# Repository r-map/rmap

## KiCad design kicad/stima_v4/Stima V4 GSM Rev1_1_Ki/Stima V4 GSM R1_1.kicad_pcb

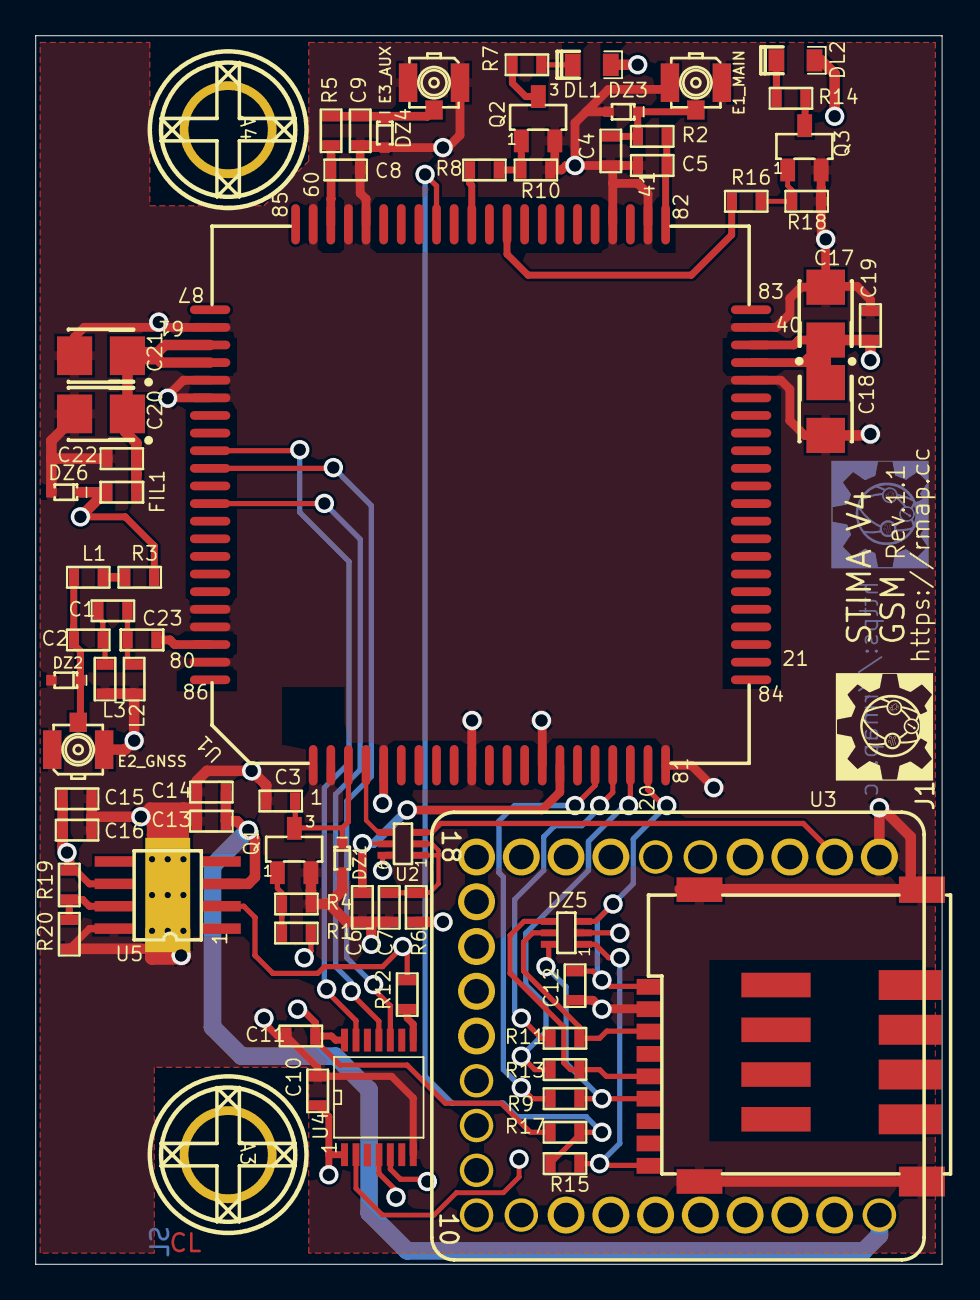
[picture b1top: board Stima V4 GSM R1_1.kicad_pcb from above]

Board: 4 copper layers, 51.4 x 69.7 mm, 69 parts (0 on the bottom side), 47 nets.

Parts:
A3, A4: ViteDado; ViteDado4
C1, C23: 0R; 0603
C2: 33pF; 0603
C3, C6, C7, C10, C11, C12, C13, C15, C19, C22: 100n; 0603
C4, C5, C8, C9: NM; 0603
C14, C16: 10uF; 0603
C17, C18, C20, C21: 100uF 10V; Case B-TC3528-1411
DL1: BLU; 0805-led
DL2: GREEN; 0805-led
DZ1: PESD5Z3.3; SOD 523(SC-79)
DZ2, DZ3, DZ4, DZ6: PESD5Z5.0; SOD 523(SC-79)
DZ5: ESDA6V1-5W6; SOT363(SC70)
E1_MAIN, E2_GNSS, E3_AUX: RECE.20279.001E.01; CONN_ANTENNA_SMD
FIL1: BLM18PG; 0603
J1: SIM7100-6-1-15-00-A; SIM CARD MICRO
L1: 7447860147G; 0603
L2, L3: NM; 0603
Q1: BSS138P; SOT23
Q2, Q3: BC817; SOT23
R1, R8, R16: 4K7; 0603
R2, R5, R13: 0R; 0603
R3: 10R; 0603
R4, R10, R17, R18: 47K; 0603
R6: 200K; 0603
R7, R14: 2K2; 0603
R9, R11, R15: 22R; 0603
R12: 47R; 0603
R19: 100K; 0603
R20: 15K; 0603
U1: SIM7600E S2-107EP-Z304M; SIM7600
U2: LSF0101GWH; SOT363(SC70)
U3: UPIN27; UPIN27_OK
U4: TXU0204; TSSOP14
U5: SC4216; SO8-EDP-2 MIO

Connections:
+1V8: C6.1, C11.1, R17.2, U1.15, U2.5, U4.14
+3V3: C10.1, R6.2, U3.2, U4.1
+3V8: C15.1, C16.1, C17.1, C18.1, C19.1, DL1.2, DL2.2, DZ6.1, FIL1.1, R3.1, R19.2, U1.38, U1.39, U5.6
+5V: C13.1, C14.1, U3.1, U5.3
EN_PW_GSM: R12.2, U3.23, U5.2
GND: C3.2, C4.2, C5.2, C6.2, C7.2, C8.2, C9.2, C10.2, C11.2, C12.2, C13.2, C14.2, C15.2, C16.2, C17.2, C18.2, C19.2, C20.2, C21.2, C22.2, DZ1.2, DZ2.2, DZ3.2, DZ4.2, DZ5.2, DZ6.2, E1_MAIN.2, E2_GNSS.2, E3_AUX.2, J1.C5, J1.GND, L2.1, L3.1, Q1.2, Q2.2, Q3.2, R4.1, R10.1, R18.1, R20.1, U1.1, U1.2, U1.5, U1.10, U1.14, U1.37, U1.40, U1.41, U1.43, U1.57, U1.58, U1.60, U1.61, U1.64, U1.65, U1.77, U1.78, U1.80, U1.81, U2.6, U3.27, U4.7, U5.0, U5.8, U5.9
NetC1_1: C1.1, C23.2, L2.2
NetC1_2: C1.2, C2.1, L3.2
NetC2_2: C2.2, DZ2.1, E2_GNSS.1, L1.1
NetC3_1: C3.1, DZ1.1, Q1.3, U1.3
NetC4_1: C4.1, DZ3.1, E1_MAIN.1, R2.2
NetC5_1: C5.1, R2.1, U1.82
NetC7_1: C7.1, R6.1, U2.1, U2.2
NetC8_1: C8.1, R5.2, U1.59
NetC9_1: C9.1, DZ4.1, E3_AUX.1, R5.1
NetC12_1: C12.1, DZ5.3, J1.C1, U1.20
NetC20_1: C20.1, C21.1, C22.1, FIL1.2, U1.62, U1.63
NetC23_1: C23.1, U1.79
NetDL1_1: DL1.1, R7.1
NetDL2_1: DL2.1, R14.1
NetDZ5_1: DZ5.1, J1.CD, R15.2
NetDZ5_4: DZ5.4, J1.C3, R13.2
NetDZ5_5: DZ5.5, J1.C2, R11.2
NetDZ5_6: DZ5.6, J1.C7, R9.2
NetL1_2: L1.2, R3.2
NetQ1_1: Q1.1, R1.1, R4.2
NetQ2_1: Q2.1, R8.1, R10.2
NetQ2_3: Q2.3, R7.2
NetQ3_1: Q3.1, R16.1, R18.2
NetQ3_3: Q3.3, R14.2
NetR8_2: R8.2, U1.51
NetR9_1: R9.1, U1.17
NetR11_1: R11.1, U1.18
NetR12_1: R12.1, U4.8
NetR13_1: R13.1, U1.19
NetR15_1: R15.1, R17.1, U1.53
NetR19_1: R19.1, R20.2, U5.7
NetU1_4: U1.4, U2.4
NetU1_68: U1.68, U4.13
NetU1_69: U1.69, U4.10
NetU1_71: U1.71, U4.11
PWRKEY: R1.2, U3.24
RI: U3.21, U4.5
RST: U2.3, U3.26
STATUS: R16.2, U1.49
USART2_RX: U3.19, U4.4
USART2_TX: U3.20, U4.2

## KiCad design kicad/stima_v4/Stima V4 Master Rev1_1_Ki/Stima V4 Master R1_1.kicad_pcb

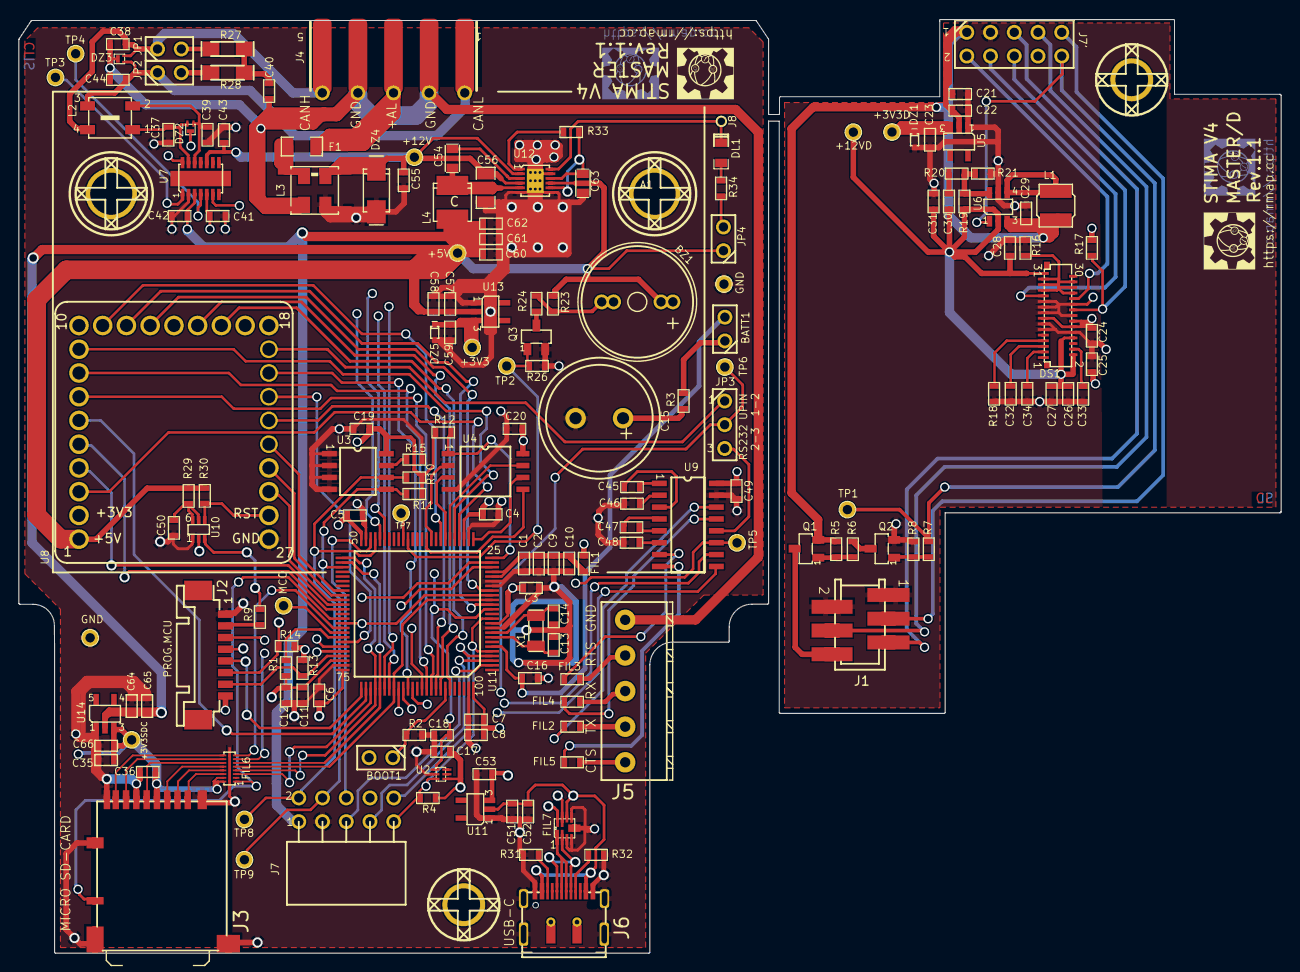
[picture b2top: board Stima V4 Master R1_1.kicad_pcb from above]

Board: 6 copper layers, 135.0 x 99.9 mm, 173 parts (0 on the bottom side), 134 nets.

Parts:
+3V3, +3V3D, +3V3SDC, +5V, +12V, +12VD: TestPoint; TP
A: Comment; _Altium_ARGO_ARGO PcbLib-Trad1.PcbLib_ViteDado4
A1: ViteDado; ViteDado4
A2, A3: ViteDado; _Altium_Library_ARGO_ARGO PcbLib-Trad1.PcbLib_ViteDado3
BATT1: Strip 2p p.2.54; STRIP2P
BOOT1: Strip 2p p.2.54; STRIP2P
BZ1: F/UCW03 (2-5V); BUZZER TDK PS1240P02CT3
C1, C3, C4, C5, C6, C7, C9, C11, C16, C17, C18, C19, C20, C22, C24, C25, C27, C28, C36, C40, C41, C42, C43, C45, C46, C47, C48, C49, C50, C52, C58, C65: 100n; 0603
C2, C10, C21, C23, C26, C29, C31, C51, C53, C57, C59, C64, C66: 1uF; 0603
C8, C12, C32, C33, C34, C35: 4.7u; 0603
C13, C14: 15pF; 0603
C15: 0.1F 5V5 FT0H104ZF; CapELSUPERCAP-3D FT0H104ZF
C30: 22p; 0603
C37, C38, C39, C44: 220p; 0603
C54: 100n; 0805
C55: 1nF; 0603
C56: 4.7u35V; 1206
C60, C61, C62: 10uF; 0603
C63: 1uF; 0805
DL1: GREEN; 0805-led
DS1: REX160128AYPP3N00000; CONN FPC_FFC 31P P0.3 REVERSE-MIO
DZ1, DZ5: PESD5Z3.3; SOD 523(SC-79)
DZ2, DZ3: ESDCAN03; QFN-3L-DFN1110-MIO
DZ4: SMAJ28A; SMA
F1: NSMF150; 1206
FIL1: BLM18BD; 0603
FIL2, FIL3, FIL4, FIL5: BLM18BD102SN1D; 0603
FIL6: EMIF06-; EMIF06MSD02N16-MIO
FIL7: EMI2121MTTAG; WDFN8 - MIO
GND: TestPoint; TP
GND#2: TestPoint; TP
J1: ENCODER+PB 62AG22-L5-040C; CONN MICROMATCH6PF MIO
J2: Pico Blade 8p 53398-0871; MOLEX8P1_25SMD
J3: 101019966912A AMPHENOL; SD CARD MICRO HIROSE MIO
J4: 5P BUS; CONTATTI5
J5: 5P; CONN_5P-P381
J6: USB TYPE C; USB TYPE C 16PIN MIO
J7: Strip 5x2-DF 90 p.2.54; _Altium_Library_ARGO_ARGO PcbLib-Trad1.PcbLib_STRIP2F5X2P2_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
J7': Strip 5x2-DF p.2.54; _Altium_Library_ARGO_ARGO PcbLib-Trad1.PcbLib_STRIP2F5X2P2_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
J8: VIAS1; VIAS0_8
JP1, JP2, JP4: Strip 2p PTH; STRIP2P
JP3: Strip 3p PTH; STRIP3PP254
L1: TYS4018; COIL LAIRD TYS4018
L2: ACT45B-110; ACT45B TDK-MIO
L3: DLW5BTM; FILTRO DLW5B MIO
L4: XAL4020; COIL COILCRAFT XAL4020-MIO
MCO: TestPoint; TP
Q1: BC807; SOT23
Q2, Q3: BSS138P; SOT23
R1: NM; 0603
R2, R4, R13: 100K; 0603
R3, R6, R23, R34: 1K; 0603
R5, R8, R12, R14, R15, R16, R17, R21, R26, R30, R33: 10K; 0603
R7: 100R; 0603
R9, R24: 0R; 0603
R10, R11, R20: 2K2; 0603
R18: 810K; 0603
R19: 110K; 0603
R27, R28: MMA0204 60R4; MELFRESMMA0204
R29: 200K; 0603
R31, R32: 5K11; 0603
TP1, TP2, TP3, TP4, TP5, TP6, TP7, TP8, TP9: TestPoint; TP
U1: STM32L496VGT6; LQFP100P05
U2: STM6519; UDFN6 - MIO
U3: CAT24C64WI; SO8
U4: AT25SF641B; SO8W
U5, U11, U13, U14: ST732M33R; SOT23_5
U6: R1202N513B; SOT23_6
U7: TJA1443ATK; HVSON14 MIO
U8: UPIN27; UPIN27_OK
U9: TRSF3232EIDR; SO16
U10: LSF0101GWH; SOT363(SC70)
U12: MAX20077; TDFN 12L MIO
X1: 32.768KHz; CRYST_ECS

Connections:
3V3USB: C11.1, C12.2, C53.1, R1.1, U1.73, U11.3
+3V3: +3V3.1, BOOT1.2, C3.2, C4.2, C5.2, C6.2, C7.2, C8.2, C17.1, C19.1, C20.1, C41.1, C49.1, C59.1, DZ5.1, FIL1.1, J2.8, R4.2, R10.2, R11.2, R12.1, R13.2, R14.2, U1.11, U1.28, U1.50, U1.75, U1.100, U2.4, U3.8, U4.8, U7.5, U8.2, U9.16, U10.2, U13.3
+3V3D: +3V3D.1, C23.1, C24.1, C25.1, DS1.12, DS1.14, DS1.15, DZ1.1, R17.1, U5.3
+3V3SDC: +3V3SDC.1, C35.1, C36.1, C66.1, FIL6.15, FIL6.16, J3.4, U14.3
+5V: +5V.1, BZ1.1, C21.1, C22.1, C29.1, C42.1, C57.1, C58.1, C60.2, C61.2, C62.2, C64.1, C65.1, J7.1, J7'.1, JP4.1, L1.1, L4.2, Q1.2, R5.2, R23.2, R29.2, R30.2, U5.2, U6.3, U7.3, U8.1, U12.9, U13.2, U14.2
+5VE: J1.6, Q1.3
+12V: +12V.1, C43.2, C55.1, C56.1, DZ4.1, L3.2, U7.10, U12.2, U12.4
+12VD: +12VD.1, C26.2, C27.2, C28.2, C30.1, C31.1, DS1.2, DS1.8, DS1.31, R19.1, U6.2
+AL: F1.1, J4.3
-RESET: C18.1, R9.1, U1.14, U2.1, U10.3
CANH: C38.2, DZ3.2, J4.5, JP1.1, L2.4
CANL: C44.2, DZ3.1, J4.1, JP2.1, L2.3
EGND: C38.1, C40.1, C44.1, DZ3.3, J4.2, J4.4, J5.5, L3.4
EN+5VE: J7.10, J7'.10, R7.2, TP1.1, U1.4, U6.1
ENC_A: J1.5, J7.5, J7'.5, U1.2
ENC_B: J1.4, J7.7, J7'.7, U1.3
GND: C1.1, C2.2, C3.1, C4.1, C5.1, C6.1, C7.1, C8.1, C9.1, C10.2, C11.2, C12.1, C13.2, C14.2, C15.2, C16.1, C17.2, C18.2, C19.2, C20.2, C21.2, C22.2, C23.2, C24.2, C25.2, C26.1, C27.1, C28.1, C29.2, C31.2, C32.2, C33.2, C34.2, C35.2, C36.2, C37.1, C39.1, C41.2, C42.2, C43.1, C46.1, C48.1, C49.2, C50.1, C51.2, C52.2, C53.2, C55.2, C56.2, C57.2, C58.2, C59.2, C60.1, C61.1, C62.1, C63.2, C64.2, C65.2, C66.2, DS1.10, DS1.11, DS1.13, DS1.16, DS1.17, DS1.19, DS1.20, DS1.21, DZ1.2, DZ2.3, DZ4.2, DZ5.2, FIL6.17, FIL7.3, FIL7.4, FIL7.5, FIL7.GND, GND.1, GND#2.1, J1.1, J1.2, J2.1, J3.6, J3.CD2, J3.SCH, J6.0, J6.A1, J6.A12, J6.B1, J6.B12, J7.3, J7'.3, L3.3, Q2.2, Q3.2, R2.1, R8.2, R15.1, R16.2, R18.1, R21.2, R26.1, R31.1, R32.2, U1.10, U1.19, U1.20, U1.27, U1.49, U1.74, U1.99, U2.2, U3.1, U3.2, U3.3, U3.4, U4.4, U5.1, U6.5, U7.2, U8.27, U9.15, U10.1, U11.1, U12.6, U12.7, U12.11, U12.13, U13.1, U14.1
KEY1: J1.3, J7.9, J7'.9, R4.1, U1.5, U1.12, U2.3
NetBATT1_1: BATT1.1, R3.1
NetBATT1_2: BATT1.2, C16.2, U1.6
NetBOOT1_1: BOOT1.1, R2.2, U1.94
NetBZ1_2: BZ1.2, R23.1, R24.1
NetC1_2: C1.2, C2.1, C9.2, C10.1, FIL1.2, U1.21, U1.22
NetC13_1: C13.1, U1.8, X1.2
NetC14_1: C14.1, U1.9, X1.1
NetC15_1: C15.1, R3.2
NetC30_2: C30.2, R20.1
NetC32_1: C32.1, DS1.5
NetC33_1: C33.1, DS1.4
NetC34_1: C34.1, DS1.3
NetC37_2: C37.2, DZ2.2, L2.1, U7.13
NetC39_2: C39.2, DZ2.1, L2.2, U7.12
NetC40_2: C40.2, R27.1, R28.2
NetC45_1: C45.1, U9.3
NetC45_2: C45.2, U9.1
NetC46_2: C46.2, U9.2
NetC47_1: C47.1, U9.5
NetC47_2: C47.2, U9.4
NetC48_2: C48.2, U9.6
NetC50_2: C50.2, R29.1, U10.5, U10.6
NetC51_1: C51.1, C52.1, FIL7.6, J6.A4, J6.A9, J6.B4, J6.B9, U11.2
NetC54_1: C54.1, U12.3
NetC54_2: C54.2, L4.1, U12.5
NetC63_1: C63.1, R33.1, U12.8, U12.10
NetDL1_1: DL1.1, J8.1, U12.12
NetDL1_2: DL1.2, R34.1
NetDS1_7: DS1.7, R18.2
NetDS1_18: DS1.18, J7.6, J7'.6, R17.2, U1.48
NetDS1_24: DS1.24, DS1.25, DS1.26, DS1.27, DS1.28, DS1.29, R16.1
NetF1_2: F1.2, L3.1
NetFIL2_1: FIL2.1, U9.14
NetFIL2_2: FIL2.2, J5.2
NetFIL3_1: FIL3.1, U9.7
NetFIL3_2: FIL3.2, J5.4
NetFIL4_1: FIL4.1, U9.13
NetFIL4_2: FIL4.2, J5.3
NetFIL5_1: FIL5.1, U9.8
NetFIL5_2: FIL5.2, J5.1
NetFIL6_1: FIL6.1, J3.CD1, U1.64
NetFIL6_3: FIL6.3, U1.78
NetFIL6_8: FIL6.8, U1.66
NetFIL6_9: FIL6.9, J3.8
NetFIL6_10: FIL6.10, J3.7
NetFIL6_11: FIL6.11, J3.5
NetFIL6_12: FIL6.12, J3.3
NetFIL6_13: FIL6.13, J3.2
NetFIL6_14: FIL6.14, J3.1
NetFIL7_1: FIL7.1, J6.A6, J6.B6
NetFIL7_2: FIL7.2, J6.A7, J6.B7
NetFIL7_7: FIL7.7, U1.70
NetFIL7_8: FIL7.8, U1.71
NetJ2_2: J2.2, R9.2
NetJ6_A5: J6.A5, R31.2
NetJ6_B5: J6.B5, R32.1
NetJP1_2: JP1.2, R27.2
NetJP2_1: JP2.2, R28.1
NetJP3_2: JP3.2, TP6.1, U1.87
NetJP3_3: JP3.3, U9.12
NetJP4_2: JP4.2, R34.2
NetL1_2: L1.2, U6.4
NetMCO_1: MCO.1, U1.67
NetQ1_1: Q1.1, R5.1, R6.1
NetQ2_1: Q2.1, R7.1, R8.1
NetQ2_3: Q2.3, R6.2
NetQ3_1: Q3.1, R26.2, TP2.1, U1.40
NetQ3_3: Q3.3, R24.2
NetR1_2: R1.2, U1.68
NetR15_2: R15.2, U3.7
NetR19_2: R19.2, R20.2, R21.1, U6.6
NetR33_2: R33.2, U12.1
NetTP3_1: TP3.1, U1.82, U7.1
NetTP4_1: TP4.1, U1.81, U7.4
NetTP7_1: TP7.1, U1.41
NetU1_15: U1.15, U8.12
NetU1_18: U1.18, U8.13
NetU1_29: U1.29, U8.3
NetU1_30: U1.30, U8.9
NetU1_33: U1.33, U8.11
NetU1_45: U1.45, U7.6
NetU1_46: U1.46, U7.14
NetU1_58: U1.58, U8.23
NetU1_59: U1.59, U8.24
NetU1_60: U1.60, U8.25
NetU1_61: U1.61, U8.4
NetU1_62: U1.62, U8.5
NetU1_69: U1.69, U8.21
NetU1_77: U1.77, U8.6
NetU1_84: U1.84, U9.9
NetU1_85: U1.85, U9.10
NetU1_90: U1.90, U8.8
NetU1_91: U1.91, U8.7
NetU1_92: U1.92, U8.22
NetU1_93: U1.93, U8.15
NetU1_95: U1.95, U8.16
PA2/F_-CS: R12.2, U1.25, U4.1
PA3/F_SCK: U1.26, U4.6
PA6/F_I/O3: U1.31, U4.7
PA7/F_I/O2: U1.32, U4.3
PA13/SWDIO: J2.7, R13.1, U1.72
PA14/SWCLK: J2.5, U1.76
PB0/F_I/O1: U1.35, U4.2
PB1/F_I/O0: U1.36, U4.5
PB3/SWO: J2.3, U1.89
PB10/I2C2_SCL: DS1.22, J7.2, J7'.2, R10.1, TP8.1, U1.47, U3.6
PB14/I2C2_SDA: DS1.23, J7.4, J7'.4, R11.1, TP9.1, U1.53, U3.5
RST: R30.1, U8.26, U10.4
SDMMC1_CK: FIL6.6, U1.52, U1.80
SDMMC1_CMD: FIL6.5, U1.16, U1.83
SDMMC1_D0: FIL6.7, U1.17, U1.65
SDMMC1_D3: FIL6.4, U1.51, U1.79
USART2_RX: JP3.1, U8.19
USART2_TX: TP5.1, U1.86, U8.20, U9.11
USART4_RX: J2.6, R14.1, U1.24
USART4_TX: J2.4, U1.23

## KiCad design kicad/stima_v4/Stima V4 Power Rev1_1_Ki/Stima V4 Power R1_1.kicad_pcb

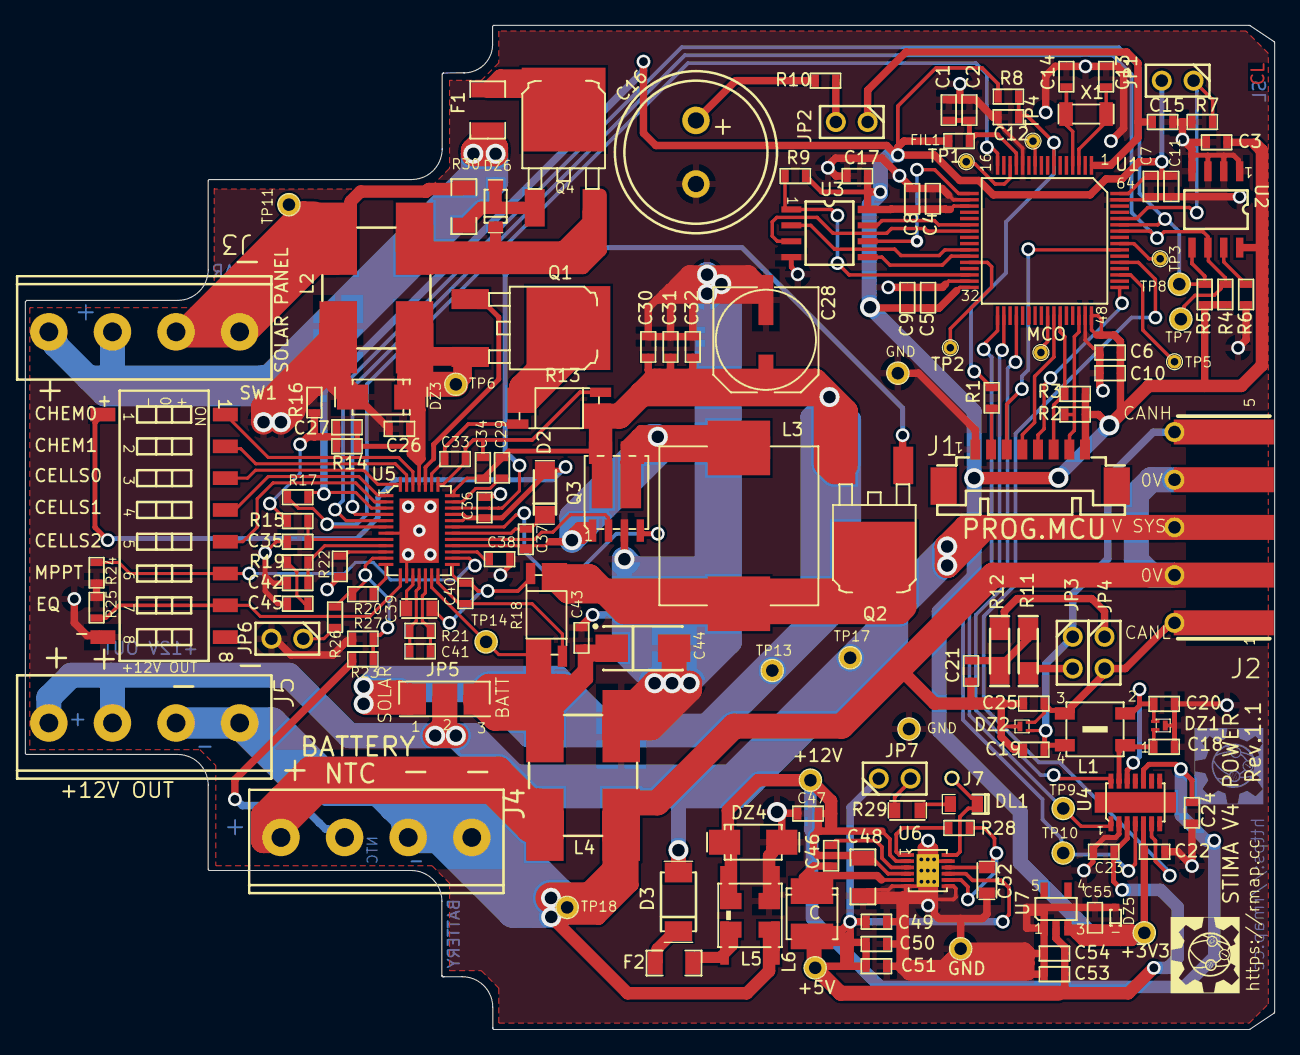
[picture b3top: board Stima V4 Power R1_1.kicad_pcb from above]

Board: 2 copper layers, 99.8 x 80.2 mm, 151 parts (0 on the bottom side), 99 nets.

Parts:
+3V3, +5V, +12V: TestPoint; TP
C1, C8, C9, C10, C11: 4.7uF; 0603
C2, C3, C4, C5, C6, C7, C12, C15, C17, C21, C22, C23, C24, C30, C41, C46, C54: 100nF; 0603
C13, C14: 15pF; 0603
C16: 0.1F 5V5; CapELSUPERCAP-3D FT0H104ZF
C18, C19, C20, C25: 220pF; 0603
C26, C31, C32, C36, C43: 10uF 35V; 0603
C27: 2.2nF; 0603
C28: 100uF 50V; 8X10_5
C29: 330nF; 0603
C33, C40, C47: 1nF; 0603
C34, C53, C55: 1uF; 0603
C35: 100pF; 0603
C37: 470nF; 0603
C38: 2.2uF; 0603
C39: 330nF; 0805
C42: 10nF; 0603
C44: 10uF 25V; Case C-TC6032-2412
C45: 220nF; 0603
C48: 4.7uF 35V; 1206
C49, C50, C51: 10uF; 0603
C52: 1uF; 0805
D2: LL4148; DSOD80
D3: SM4007; QMELFD
DL1: VERDE; 0805-led
DZ1, DZ2: ESDCAN03-2BM3Y; QFN-3L-DFN1110-MIO
DZ3, DZ4: SMAJ28A; SMA
DZ5: PESD5Z3.3; SOD 523(SC-79)
DZ6: BZT52C10; SOD-123
F1: MMF-USML600/6-2; 1210
F2: MF-NSMF150; 1206
FIL1: BLM18BD102SN1D; 0603
GND: TestPoint; TP
GND#2, GND#3: TestPoint; TP
J1: Pico Blade 8p 53398-0871; MOLEX8P1_25SMD
J2: 5P BUS; CONTATTI5
J3, J4, J5: 4P; CONN_4P-P508
J7: VIAS1; VIAS0_8
JP1, JP2, JP3, JP4, JP6: Strip 2p PTH; STRIP2P
JP5: JUMP3S
JP7: Strip 2p trad.; STRIP2P
L1: ACT45B-110-2P-TL003; ACT45B TDK-MIO
L2, L4: SBS9080-509T; FILTRO KEMET SBS9080-MIO
L3: SRP1265A-100M; COIL BOURNS SRP1265A-MIO
L5: DLW5BTM142TQ2L; FILTRO DLW5B MIO
L6: XAL4020-222MEC; COIL COILCRAFT XAL4020-MIO
MCO: TestPoint; TP_P
Q1: DMTH43M8LK3Q-13; TO252 (DPAK)
Q2: SQD40131EL_GE3; TO252 (DPAK)
Q3: DMTH4011SPD-13; POWERDI5060-8-MIO
Q4: DMPH6050SK3-13; TO252 (DPAK)
R1: 0R; 0603
R2, R7, R8: 100K; 0603
R3, R6, R9, R15, R16, R17, R20, R24, R25, R26, R28: 10K; 0603
R4, R5: 2K2; 0603
R10: 1K; 0603
R11, R12: MMA0204 60R4; MELFRESMMA0204
R13, R18: WSK2512 10mOHM; RES CURRSENS 4P WSK2512
R14: 294K; 0603
R19: 200R; 0603
R21: 301K 0.1%; 0603
R22: 95K3; 0603
R23, R27: *; 0603
R29: 1K; 0805
R30: 1K5 1/2W; 1206
SW1: TDS08SGNNTR04; DIPSWITCH8P-TRISTATE
TP1, TP2, TP3, TP4, TP5: TestPoint; TP_P
TP6, TP7, TP8, TP9, TP10, TP11, TP13, TP14, TP17, TP18: TestPoint; TP
U1: STM32L452RCT6; LQFP64
U2: CAT24C64WI; SO8
U3: AT25SF161SSHD; SO8
U4: TJA1443ATK; HVSON14 MIO
U5: LTC4015EUHF#PBF; UHF QFN38 MIO
U6: MAX20077ATCA/VY+; TDFN 12L MIO
U7: ST732M33R; SOT23_5
X1: 32.768KHz; CRYST_ECS

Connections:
+: J4.1, L4.1
+3V3: +3V3.1, C3.1, C4.1, C5.1, C6.1, C7.1, C8.2, C9.2, C10.2, C11.2, C17.1, C22.1, C55.1, DZ5.1, FIL1.1, J1.8, JP1.2, R2.1, R3.1, R4.2, R5.2, R8.2, R9.2, R17.1, U1.19, U1.32, U1.48, U1.64, U2.8, U3.8, U4.5, U5.3, U7.3
+5V: +5V.1, C23.1, C49.2, C50.2, C51.2, C53.1, C54.1, JP7.1, L6.2, U4.3, U6.9, U7.2
+12V: +12V.1, C24.2, C47.1, C48.1, DZ4.1, L5.2, U4.10, U6.2, U6.4
-: C19.1, C21.1, C25.1, DZ2.3, J2.2, J2.4, J4.3, J4.4, J5.3, J5.4, L4.3, L5.4, TP18.1
-RESET: C12.1, R1.1, R8.1, U1.7
CANH: C19.2, DZ2.1, J2.5, JP3.1, L1.4
CANL: C25.2, DZ2.2, J2.1, JP4.2, L1.3
F_-CS: R9.1, U1.30, U3.1
F_I/O0: U1.27, U3.5
F_I/O1: U1.26, U3.2
F_I/O2: U1.23, U3.3
F_I/O3: U1.22, U3.7
F_SCK: U1.17, U3.6
GND: C1.2, C2.2, C3.2, C4.2, C5.2, C6.2, C7.2, C8.1, C9.1, C10.1, C11.1, C12.2, C13.2, C14.2, C15.2, C16.2, C17.2, C18.1, C20.1, C22.2, C23.2, C24.1, C26.2, C28.2, C30.2, C31.2, C32.2, C35.2, C36.2, C38.2, C42.2, C43.2, C44.2, C45.2, C47.2, C48.2, C49.1, C50.1, C51.1, C52.1, C53.2, C54.2, C55.2, DZ1.3, DZ3.2, DZ4.2, DZ5.2, GND.1, GND#2.1, GND#3.1, J1.1, JP6.2, L2.4, L4.4, L5.3, Q3.S2, R6.1, R7.2, R16.1, R22.1, R24.1, R25.1, R27.2, SW1.-, U1.12, U1.18, U1.31, U1.47, U1.63, U2.1, U2.2, U2.3, U2.4, U3.4, U4.2, U5.7, U5.14, U5.39, U6.6, U6.7, U6.11, U6.13, U7.1
I2C1_SCL: R4.1, TP7.1, U1.58, U2.6, U5.4
I2C1_SDA: R5.1, TP8.1, U1.59, U2.5, U5.5
INTVCC: C36.1, D2.2, SW1.+, U5.27, U5.28
NTC: J4.2, R23.1
NetC1_1: C1.1, C2.1, FIL1.2, U1.13
NetC13_1: C13.1, U1.3, X1.2
NetC14_1: C14.1, U1.4, X1.1
NetC15_1: C15.1, JP2.1, U1.1
NetC16_1: C16.1, R10.2
NetC18_2: C18.2, DZ1.2, L1.1, U4.13
NetC20_2: C20.2, DZ1.1, L1.2, U4.12
NetC21_2: C21.2, R11.1, R12.2
NetC26_1: C26.1, C27.1, DZ3.1, L2.2, Q1.3, R14.2, TP6.1, U5.35
NetC27_2: C27.2, R14.1, R15.1, R16.2
NetC28_1: C28.1, C29.1, C30.1, C31.1, C32.1, C34.2, JP5.1, Q2.3, Q3.D1, R13.I2, TP13.1, U5.31
NetC29_2: C29.2, U5.30
NetC33_1: C33.1, R13.E1, U5.33
NetC33_2: C33.2, C34.1, R13.E2, U5.32
NetC35_1: C35.1, R15.2, U5.8
NetC37_1: C37.1, D2.1, U5.25
NetC37_2: C37.2, L3.1, Q3.D2, Q3.S1, U5.23
NetC38_1: C38.1, U5.22
NetC39_1: C39.1, U5.15
NetC39_2: C39.2, C40.1, R18.E1, U5.20
NetC40_2: C40.2, R18.E2, U5.19
NetC41_1: C41.1, R21.2, U5.17
NetC41_2: C41.2, R21.1, U5.16
NetC42_1: C42.1, R19.2, U5.9
NetC43_1: C43.1, C44.1, JP5.3, L4.2, R18.I2, TP14.1, U5.18
NetC45_1: C45.1, R19.1
NetC46_1: C46.1, U6.3
NetC46_2: C46.2, L6.1, U6.5
NetC52_2: C52.2, R28.2, U6.8, U6.10
NetD3_1: D3.1, F2.1
NetDL1_1: DL1.1, J7.1, U6.12
NetDL1_2: DL1.2, R29.1
NetDZ6_1: DZ6.1, L2.1, Q4.3
NetDZ6_2: DZ6.2, Q4.1, R30.2
NetF1_1: F1.1, J3.3, J3.4
NetF1_2: F1.2, Q4.2
NetF2_2: F2.2, L5.1
NetJ1_2: J1.2, R1.2
NetJ3_1: J3.1, J3.2, L2.3, R30.1, TP11.1
NetJP1_1: JP1.1, R7.1, U1.60
NetJP2_2: JP2.2, R10.1
NetJP3_2: JP3.2, R11.2
NetJP4_1: JP4.1, R12.1
NetJP6_1: JP6.1, R26.1
NetJP7_2: JP7.2, R29.2
NetL3_2: L3.2, Q2.2, R18.I1
NetMCO_1: MCO.1, U1.41
NetQ1_1: Q1.1, U5.34
NetQ1_2: Q1.2, R13.I1
NetQ2_1: Q2.1, U5.29
NetQ3_G1: Q3.G1, U5.24
NetQ3_G2: Q3.G2, U5.26
NetR6_2: R6.2, U2.7
NetR17_2: R17.2, U1.16, U5.6
NetR20_1: R20.1, R23.2, R26.2, R27.1, U5.11
NetR20_2: R20.2, U5.12
NetR22_2: R22.2, U5.10
NetR24_2: R24.2, SW1.6, U5.21
NetR25_2: R25.2, SW1.7, U5.13
NetR28_1: R28.1, U6.1
NetSW1_1: SW1.1, U5.36
NetSW1_2: SW1.2, U5.37
NetSW1_3: SW1.3, U5.38
NetSW1_4: SW1.4, U5.1
NetSW1_5: SW1.5, U5.2
NetTP1_1: TP1.1, U1.14
NetTP2_1: TP2.1, U1.28
NetTP3_1: TP3.1, U1.56
NetTP4_1: TP4.1, U1.10
NetTP5_1: TP5.1, U1.51
NetTP9_1: TP9.1, U1.34, U4.1
NetTP10_1: TP10.1, U1.33, U4.4
NetU1_36: U1.36, U4.14
NetU1_53: U1.53, U4.6
RXD: J1.6, R3.2, U1.43
SWCLK: J1.5, U1.49
SWDIO: J1.7, R2.2, U1.46
SWO: J1.3, U1.55
SYSTEM: D3.2, J2.3, J5.1, J5.2, JP5.2, TP17.1
TXD: J1.4, U1.42
